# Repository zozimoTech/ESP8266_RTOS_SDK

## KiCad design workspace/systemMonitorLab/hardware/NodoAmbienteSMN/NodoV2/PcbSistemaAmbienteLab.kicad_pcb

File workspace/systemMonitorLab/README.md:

# systemMonitorLab
- Versión README 1.3
- Version Firmware v1.3
- Autor: Ing. Cristian Aranda
- Contacto: zozimotech@gmail.com

# Resumen
Este proyecto implementa un nodo de temperatura, humedad y presión, basado en el ESP8266 y los sensores AHT10, BMP280 y DHT22. Envía las mediciones a un servidor de desarrollo propio, denominado systemMonitorServer, mediante WebSocket. El nodo está diseñado para ser configurado fácilmente a través de un menú de configuración y permite la calibración futura de los sensores. También incluye en hardware y el diseño 3D de una carcasa para proteger el nodo y los sensores.

## 1. Requisitos

Antes de comenzar, debe contar con:

- Una placa ESP8266 compatible con este proyecto.
- Un sensor DHT22.
- Un sensor AHT10.
- Un sensor BMP280.
- Un cable USB de datos para conectar la placa a la computadora.
- El repositorio del ESP8266 RTOS SDK descargado desde ZozimoTech (solicitar acceso a zozimotech@gmail.com)
- El toolchain del ESP8266 instalado y disponible en el entorno.
- Python y las dependencias indicadas por el SDK instaladas.
- Acceso a la red Wi-Fi configurada para el nodo.
- Un servidor WebSocket disponible en la red local con IP privada o en VPS con IP publica.
- Python 3.10.20 instalado.

Este proyecto usa el sistema de compilacion basado en `make`. Los
comandos deben ejecutarse desde la carpeta del proyecto, no desde la raiz del
SDK. Para mas detalle ver [ESP8266_RTOS_SDK](https://docs.espressif.com/projects/esp8266-rtos-sdk/en/latest/get-started/index.html).

## 2. Ubicacion del proyecto

El proyecto debe estar dentro del SDK o debe tener correctamente definida la
variable `IDF_PATH`. Una ubicacion recomendada es:

```text
ESP8266_RTOS_SDK/
└── workspace/
    └── systemMonitorLab/
```

Entre a la carpeta del proyecto:

```bash
cd /ruta/al/ESP8266_RTOS_SDK/workspace/systemMonitorLab
```

Compruebe que el SDK este configurado:

```bash
echo $IDF_PATH
```

El resultado debe apuntar a la carpeta del ESP8266 RTOS SDK. Si es necesario,
configure el entorno, adaptando las rutas a su instalacion:

```bash
export IDF_PATH="$HOME/esp/ESP8266_RTOS_SDK"
export PATH="$HOME/esp/xtensa-lx106-elf/bin:$PATH"
```

Si el SDK incluye un script de exportacion, tambien puede ejecutarlo:

```bash
source "$IDF_PATH/export.sh"
```

## 3. Preparar Python y sus dependencias

Este proyecto utiliza Python 3.10.20. El SDK incluye las dependencias
necesarias en:

```text
$IDF_PATH/requirements.txt
```

En Linux es recomendable crear un entorno virtual para no mezclar las
dependencias del SDK con las del sistema. Desde la carpeta del proyecto,
ejecute:

```bash
python3.10 -m venv .venv
source .venv/bin/activate
python --version
python -m pip install --upgrade pip
python -m pip install -r "$IDF_PATH/requirements.txt"
```

La salida de `python --version` debe indicar Python 3.10.20 o una version
compatible con la instalacion del proyecto.

Cada vez que abra una terminal nueva, active el entorno antes de trabajar:

```bash
cd /ruta/al/ESP8266_RTOS_SDK/workspace/systemMonitorLab
source .venv/bin/activate
```

Para salir del entorno virtual:

```bash
deactivate
```

### Hacer que `python` apunte a Python 3

Algunas herramientas del SDK invocan el comando `python`. En Linux puede crear
un alias temporal en `~/.bashrc` o `~/.profile`:

```bash
alias python='python3.10'
```

Si en su sistema el ejecutable se llama `python3` en lugar de `python3.10`,
utilice:

```bash
alias python='python3'
```

Luego cargue nuevamente la configuracion:

```bash
source ~/.bashrc
```

Si necesita que el enlace exista para todo el sistema, puede crear un enlace
simbolico. Esta alternativa modifica `/usr/bin`, por lo que requiere permisos
de administrador y debe usarse solo si no existe ya otro comando `python`:

```bash
sudo ln -s /usr/bin/python3 /usr/bin/python
```

El alias o el enlace solo resuelven el nombre del comando. El entorno virtual
sigue siendo recomendable porque mantiene separadas las versiones de los
paquetes requeridos por el SDK.

## 4. Conectar el nodo por USB

Conecte la placa ESP8266 mediante un cable USB de datos. Identifique el puerto
serie asignado por Linux:

```bash
ls /dev/ttyUSB* /dev/ttyACM* 2>/dev/null
```

Los puertos mas habituales son `/dev/ttyUSB0` o `/dev/ttyACM0`. Si no aparece
ningun puerto, revise el cable, el conversor USB-serie y los permisos del
usuario sobre el dispositivo.

## 5. Configurar el firmware

Desde la carpeta `systemMonitorLab`, ejecute:

```bash
make menuconfig
```

En el menu configure los siguientes valores.

### System Monitor Configuration

- `Node number`: numero del nodo, entre `0` y `255`.
- `WiFi SSID`: nombre de la red Wi-Fi.
- `WiFi password`: contraseña de la red Wi-Fi.
- `IP Version`: seleccione `IPV4` o `IPV6`.
- `IPV4 Address`: direccion IP del servidor si eligio IPv4.
- `IPV6 Address`: direccion IPv6 del servidor si eligio IPv6.
- `Port`: puerto TCP del servidor WebSocket.
- `Sample Rate`: intervalo de muestreo de los sensores, en segundos.
- `Transmission Rate`: intervalo de transmision al servidor, en segundos.

El intervalo de muestreo debe ser menor que el intervalo de transmision. Por
ejemplo:

```text
Sample Rate       = 10 segundos
Transmission Rate = 60 segundos
```

### Calibration Parameters

El menu `Calibration Parameters` contiene los valores que se utilizaran en el
futuro para calibrar las mediciones mediante una funcion lineal:

```text
valor_calibrado = pendiente * valor_medido + offset
```

Configure, si corresponde:

- `Pressure offset` y `Pressure slope`.
- `Temperature offset` y `Temperature slope`.
- `Humidity offset` y `Humidity slope`.

En esta version los parametros quedan guardados como configuracion y estan
disponibles como macros `CONFIG_APP_CALIBRATION_*`, pero todavia no se aplican
a las mediciones de los sensores.

### Serial Flasher Options

- Configure `Default serial port` con el puerto detectado, por ejemplo:
  `/dev/ttyUSB0`.
- Verifique la velocidad de monitor serie configurada por el proyecto.

Guarde los cambios y salga de `menuconfig`. La configuracion queda guardada en
el archivo `sdkconfig` del proyecto.

## 6. Compilar el firmware

Compile desde la carpeta del proyecto:

```bash
make
```

Para una compilacion limpia, si fuera necesario:

```bash
make clean
make
```

Si el SDK informa que faltan paquetes de Python, instale las dependencias del
SDK en el entorno correspondiente y vuelva a ejecutar el comando de
compilacion.

## 7. Grabar el ESP8266

Con la placa conectada por USB y el puerto configurado, ejecute:

```bash
make flash
```

Este comando compila lo necesario y graba el firmware en el ESP8266. Si el
puerto no fue configurado en `menuconfig`, puede indicarlo en la linea de
comandos:

```bash
make ESPPORT=/dev/ttyUSB0 flash
```

Reemplace `/dev/ttyUSB0` por el puerto real de su equipo.

## 8. Ver la salida del nodo

Para grabar el firmware y abrir el monitor serie en un solo paso:

```bash
make flash monitor
```

Tambien puede abrir el monitor despues de grabar:

```bash
make monitor
```

Para salir del monitor serie, presione:

```text
Ctrl-]
```

En el monitor deberian observarse mensajes de inicio, conexion Wi-Fi,
conexion WebSocket y transmision de mediciones.

## 9. Funcionamiento del nodo

Al iniciar, el nodo realiza estas tareas:

1. Inicializa los sensores y el bus I2C.
2. Se conecta a la red Wi-Fi configurada.
3. Sincroniza la fecha y hora mediante SNTP.
4. Intenta conectarse al servidor WebSocket.
5. Envia las mediciones segun el intervalo configurado.
6. Envia mensajes keep-alive mientras la conexion WebSocket permanece activa.
7. Intenta reconectar si falla la conexion o una transmision.

El numero de nodo se incluye en los mensajes enviados al servidor. El payload
tiene este formato:

```text
{"message":"M;numero_nodo;contador;fecha;hora;temp_dht22;temp_bmp280;humedad_dht22;presion_bmp280;"}
```

## 10. Indicadores LED

Los LED de estado indican la conectividad del nodo:

- Rojo: el nodo no tiene conexion Wi-Fi.
- Naranja: hay conexion Wi-Fi, pero no hay conexion WebSocket.
- Verde: la conexion WebSocket esta activa.
- Destellos amarillos: se transmitio una medicion.

Los GPIO de los LED y el duty de la mezcla de color pueden configurarse desde
`System Monitor Configuration` si los pines de la placa son diferentes.

## 11. Problemas frecuentes

### No aparece el puerto USB

- Use un cable USB de datos.
- Desconecte y vuelva a conectar la placa.
- Revise `dmesg` y vuelva a listar `/dev/ttyUSB*` y `/dev/ttyACM*`.
- Verifique los permisos del usuario sobre el puerto serie.

### `make menuconfig` no muestra Calibration Parameters

Verifique que existan estos archivos:

```text
components/calibration/CMakeLists.txt
components/calibration/component.mk
components/calibration/Kconfig.projbuild
```

El archivo `component.mk` es necesario porque este SDK utiliza el sistema de
componentes antiguo basado en Make.

### El nodo no conecta al servidor

- Verifique el SSID y la contraseña.
- Verifique la version IP seleccionada.
- Verifique la direccion y el puerto del servidor.
- Confirme que el servidor este iniciado y accesible desde la misma red.
- Revise los mensajes de `make monitor`.

### El build informa dependencias Python faltantes

Ejecute la instalacion de dependencias indicada por el SDK y luego vuelva a
compilar. El comando habitual es:

```bash
python -m pip install -r "$IDF_PATH/requirements.txt"
```

Si utiliza un entorno virtual del SDK, active ese entorno antes de ejecutar el
comando.

## 12. Calibracion futura

Los parametros de offset y pendiente ya pueden configurarse desde
`Calibration Parameters`. La tarea pendiente es aplicar esos valores en las
tareas de lectura del BMP280, AHT10 y DHT22.

La calibracion prevista es:

- Temperatura y humedad en una camara de temperatura y humedad.
- Presion en una camara de presion.
- Obtencion del offset y la pendiente para cada magnitud.
- Carga de los valores en `menuconfig`.
- Recompilacion y nuevo flasheo del nodo.

## 13. Hardware y gabinete

El proyecto incluye el diseño completo del nodo ambiente, separado del codigo
del firmware en las carpetas `hardware/` y `case3d/`.

### Diseño electronico

La carpeta `hardware/` contiene la documentacion y los recursos del hardware
del sistema. Incluye, entre otros elementos:

- `hardware/NodoAmbienteSMN/NodoV1`: primera version del diseño del nodo.
- `hardware/NodoAmbienteSMN/NodoV2`: version actual del diseño electronico.
- `hardware/Documentos`: documentacion, hojas de datos e insumos del sistema.
- `hardware/Pruebas`: resultados y graficos de pruebas de los sensores.
- `hardware/3DCase`: recursos asociados al diseño mecanico del nodo.

El hardware electronico fue desarrollado en KiCad. La version actual del
diseno es la v2.0 y corresponde a un PCB modular, pensado para facilitar la
integracion o el reemplazo de los sensores y perifericos del nodo ambiente.
En la carpeta de la version correspondiente se encuentran los archivos del
esquematico, el PCB y los recursos necesarios para revisar o continuar el
diseno.

### Gabinete 3D

El diseño del gabinete se encuentra en `case3d/` y en los recursos relacionados
dentro de `hardware/3DCase/`. El archivo principal actualmente disponible es:

```text
case3d/caseNodo.scad
```

El gabinete fue desarrollado mediante herramientas CAD, utilizando CadQuery y
FreeCAD para el modelado y la preparacion del diseño mecanico. La version
actual del gabinete es la v1.2.

El gabinete esta pensado para alojar el PCB modular, el ESP8266, los sensores
y sus conexiones, manteniendo accesibles los puntos necesarios para el montaje
y la operacion del nodo.

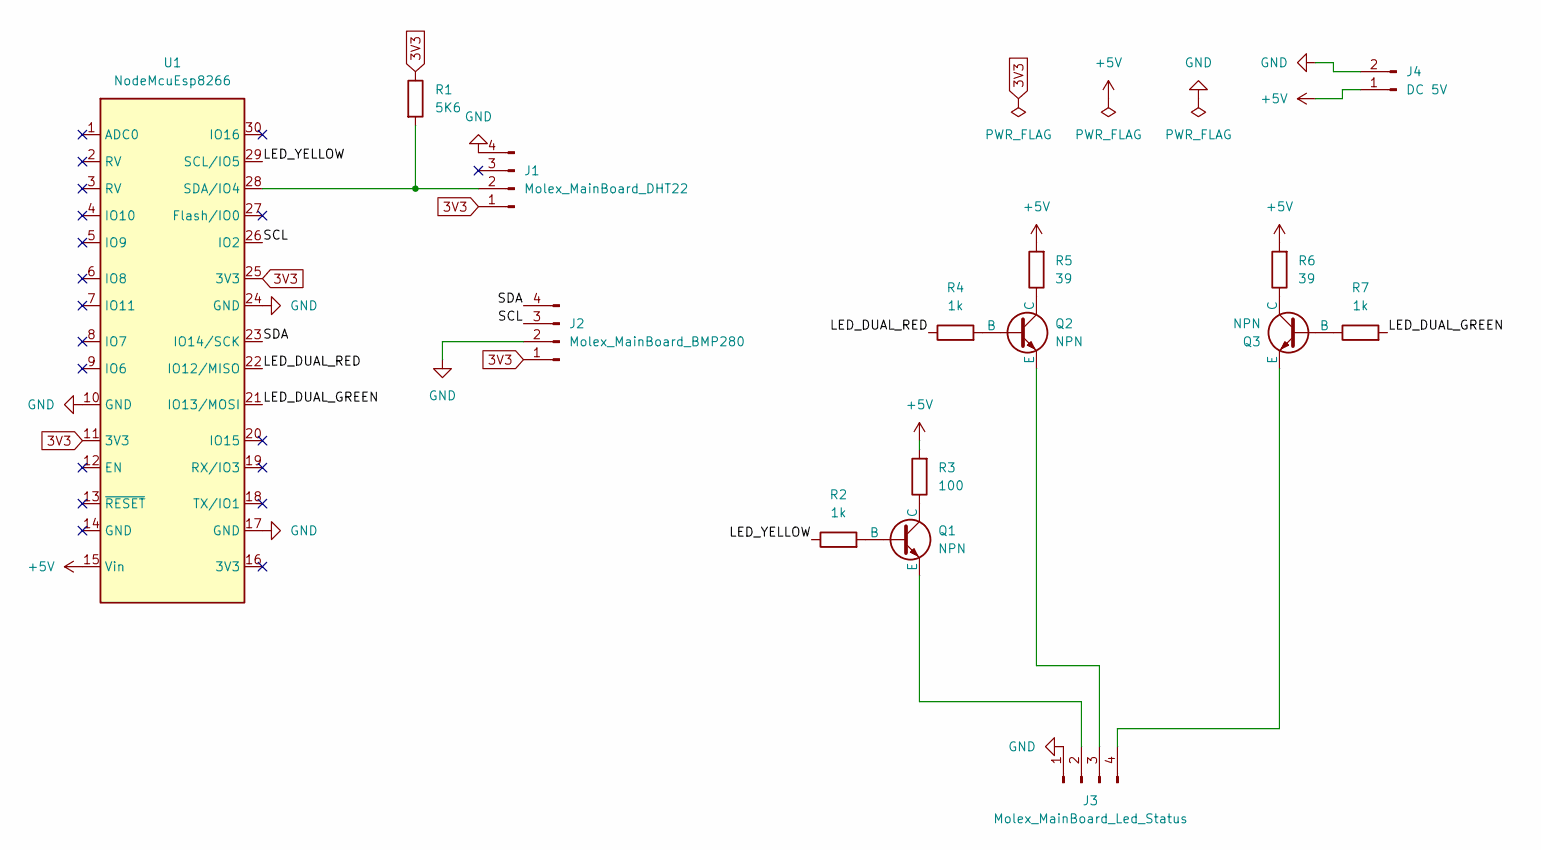
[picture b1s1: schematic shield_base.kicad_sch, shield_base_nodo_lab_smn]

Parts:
J1: Molex_MainBoard_DHT22; PinHeader_1x04_P2.54mm_Horizontal
J2: Molex_MainBoard_BMP280; PinHeader_1x04_P2.54mm_Horizontal
J3: Molex_MainBoard_Led_Status; PinHeader_1x04_P2.54mm_Horizontal
J4: DC 5V; PinHeader_1x02_P2.54mm_Horizontal
Q1, Q2, Q3: NPN; SOT-23
R1: 5K6; R_1206_3216Metric
R2, R4, R7: 1k; R_1206_3216Metric
R3: 100; R_1206_3216Metric
R5, R6: 39; R_1206_3216Metric
U1: NodeMcuEsp8266; ESP8266_v3

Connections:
3V3: J1.1, J2.1, R1.1, U1.11 (3V3), U1.25 (3V3); also elsewhere on the board
+5V: J4.1, R3.2, R5.2, R6.2, U1.15 (Vin)
/shield_base/LED_DUAL_GREEN: R7.2, U1.21 (IO13/MOSI)
/shield_base/LED_DUAL_RED: R4.1, U1.22 (IO12/MISO)
/shield_base/LED_YELLOW: R2.1, U1.29 (SCL/IO5)
/shield_base/SCL: J2.3, U1.26 (IO2)
/shield_base/SDA: J2.4, U1.23 (IO14/SCK)
GND: J1.4, J2.2, J3.1, J4.2, U1.10 (GND), U1.17 (GND), U1.24 (GND); also elsewhere on the board
unnamed: J1.2, R1.2, U1.28 (SDA/IO4)
unnamed: J3.2, Q1.3 (E)
unnamed: J3.3, Q2.3 (E)
unnamed: J3.4, Q3.3 (E)
unnamed: Q1.2 (B), R2.2
unnamed: Q1.1 (C), R3.1
unnamed: Q2.2 (B), R4.2
unnamed: Q2.1 (C), R5.1
unnamed: Q3.2 (B), R7.1
unnamed: Q3.1 (C), R6.1

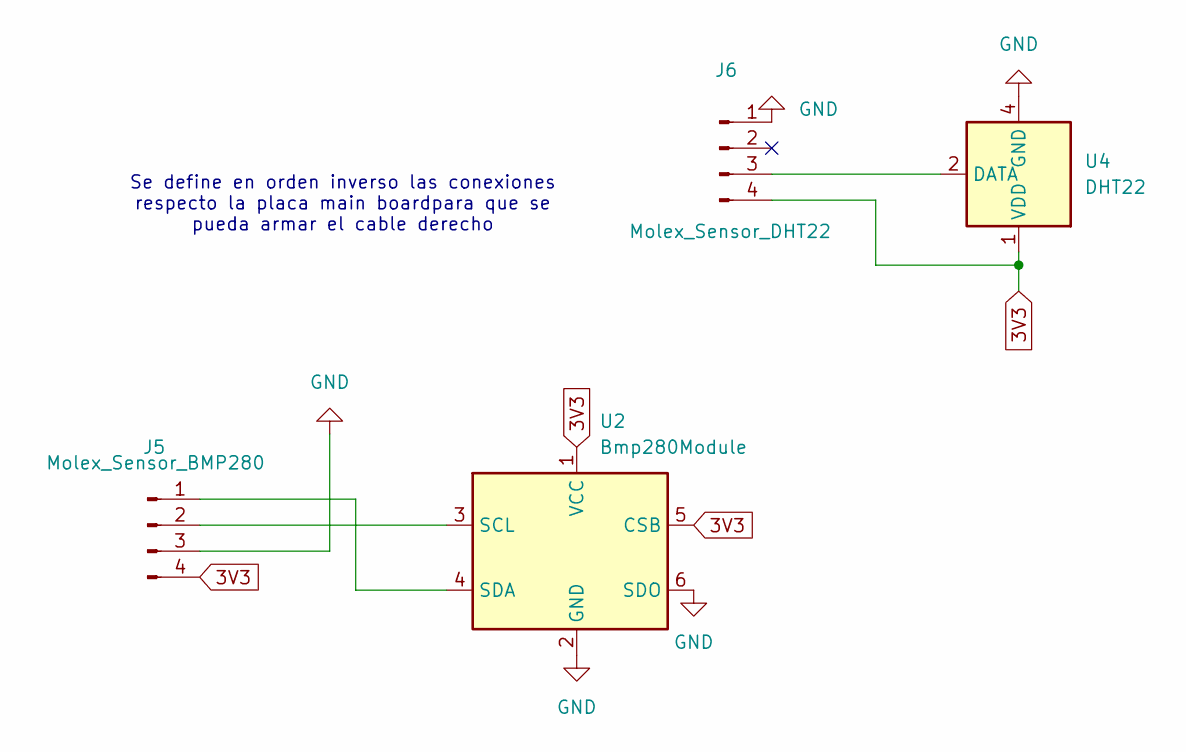
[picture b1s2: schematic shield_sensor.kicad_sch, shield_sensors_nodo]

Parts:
J5: Molex_Sensor_BMP280; PinHeader_1x04_P2.54mm_Horizontal
J6: Molex_Sensor_DHT22; PinHeader_1x04_P2.54mm_Horizontal
U2: Bmp280Module; BMP280_Module
U4: DHT22; Aosong_DHT11_5.5x12.0_P2.54mm

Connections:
3V3: J5.4, J6.4, U2.1 (VCC), U2.5 (CSB), U4.1 (VDD); also elsewhere on the board
GND: J5.3, J6.1, U2.2 (GND), U2.6 (SDO), U4.4 (GND); also elsewhere on the board
unnamed: J5.1, U2.4 (SDA)
unnamed: J5.2, U2.3 (SCL)
unnamed: J6.3, U4.2 (DATA)

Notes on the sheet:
Se define en orden inverso las conexiones respecto la placa main boardpara que se pueda armar el cable derecho

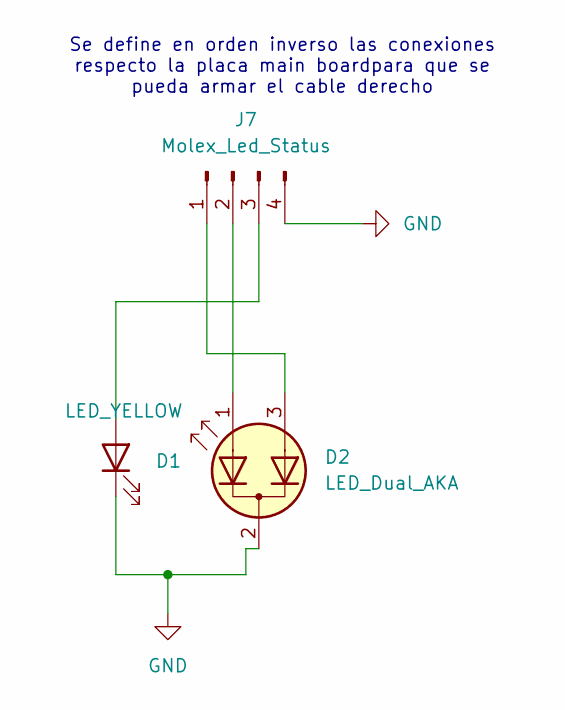
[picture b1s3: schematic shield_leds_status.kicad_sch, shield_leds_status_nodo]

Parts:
D1: LED_YELLOW; LED_D3.0mm
D2: LED_Dual_AKA; LED_D3.0mm-3
J7: Molex_Led_Status; PinHeader_1x04_P2.54mm_Horizontal

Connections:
GND: D1.1 (K), D2.2 (K), J7.4; also elsewhere on the board
unnamed: D1.2 (A), J7.3
unnamed: D2.1 (A1), J7.2
unnamed: D2.3 (A2), J7.1

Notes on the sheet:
Se define en orden inverso las conexiones respecto la placa main boardpara que se pueda armar el cable derecho

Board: 2 copper layers, 22 parts (0 on the bottom side), 24 nets, no tracks yet.

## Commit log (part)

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2025-02-26 Se termino de generar el diseño de la placa shield_main_board.
2025-02-26 Subo modificaciones en el PCB shield_sensors
2025-02-27 Borro un archivo de backup que no permite descargar el repo
2025-02-27 Actulizamos pcbs de nodo ambiente v2
2025-02-27 Agregamos el pcb de los Leds, el siguiente paso es ver los conectores Molex comerciales y ajustar el PCB en base a esa dimensiones
2025-03-02 Se va a cambiar el jack del PCB por un molex 2x1
2025-03-10 Vamos agregando la lista proveedores a la lista de componentes
2025-03-28 Se termino de diseñar la version 2 del nodo ambiente, ahora se va a diseñar el case3d para que contenga al mismo
2025-04-15 Subo el resideño de los pcb's acorde al case 3d
2025-04-25 Cambiamos de IP del servidor WebSocket, ya que desde ahora la app web esta instalada en la raspberry pi con IP 10.10.13.138, entonces se modifico en transmision.c y en la configuracion de la aplicaci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
2025-05-10 Tareas Realizadas: - Se corrije la disposicion de los conectores, para que el cable quede derecho en su construccion se tiene que invertir el orden de los pines en las placas led_status y sensors. - 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
2025-06-13 Agrego los negativos para su impresion
2025-06-17 Se actualiza el pcb de sensores
2025-06-17 Se agrega un entorno virtual de python para compilar y fhashear los ESP8266
2025-07-01 Subo una pequeña modificación
2025-07-02 probar el main con un esp32
2025-08-23 Se mejora el plano de masa del PCB
2025-08-23 Borro un archivo
2025-08-23 borramos los .lck
2026-03-22 Actualizamos el case y el pcb
2026-03-22 Agregamos el nombre del entorno virtual, ademas solo funciona con python 3.10 o menor.
2026-03-30 Se actualiza el README del proyecto systemMonitorLab
